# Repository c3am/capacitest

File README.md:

# capacitest
A low cost dual cell battery capacity tester with an oled screen using the ch32v003 microcontroller.

# discharge-tester (old version, unfinished)
In the discharge-tester directory is a pcb with mosfets used as variable resistors for discharging the cells.
It uses LMV358's as current sense amplifiers across 1 Ohm current sense resistors.
I did not get this setup to work, because the built-in adc gave me very jittery values.
Maybe there is something wrong with my circuit, or you just have to software filter the adc values.

# bidirectional-tester (current version, under development)
This is the newer version, which uses bidirectional buck-boost converters for charging the cells from an external ~12V battery/discharging them into that battery.

- ADS 1115 for current and voltage sensing
- ina181a2 + ref2020(2V Vref) for current sense amplification
- ir2101 low+high side mosfet drivers
- ceramic capacitors only
- the two bidirectional buck-/boost-converters each have 1uH SMD inductors, 200uF on the cell and 66uF capacitance on the ~12V battery side
- 0.9" i2c oled screen

## development status/roadmap:
| step                          | status        |
| ----------------------------- | ------------- |
| schematic design              | [done]        |
| PCB design                    | [done]        |
| get PCB and other components  | [done]        |
| assemble board                | [...]         |
| test board/write code         | [not started] |
| if not working, repeat        |               |
| finalize code and put online  | [not started] |

(last updated: 2025-05-08)

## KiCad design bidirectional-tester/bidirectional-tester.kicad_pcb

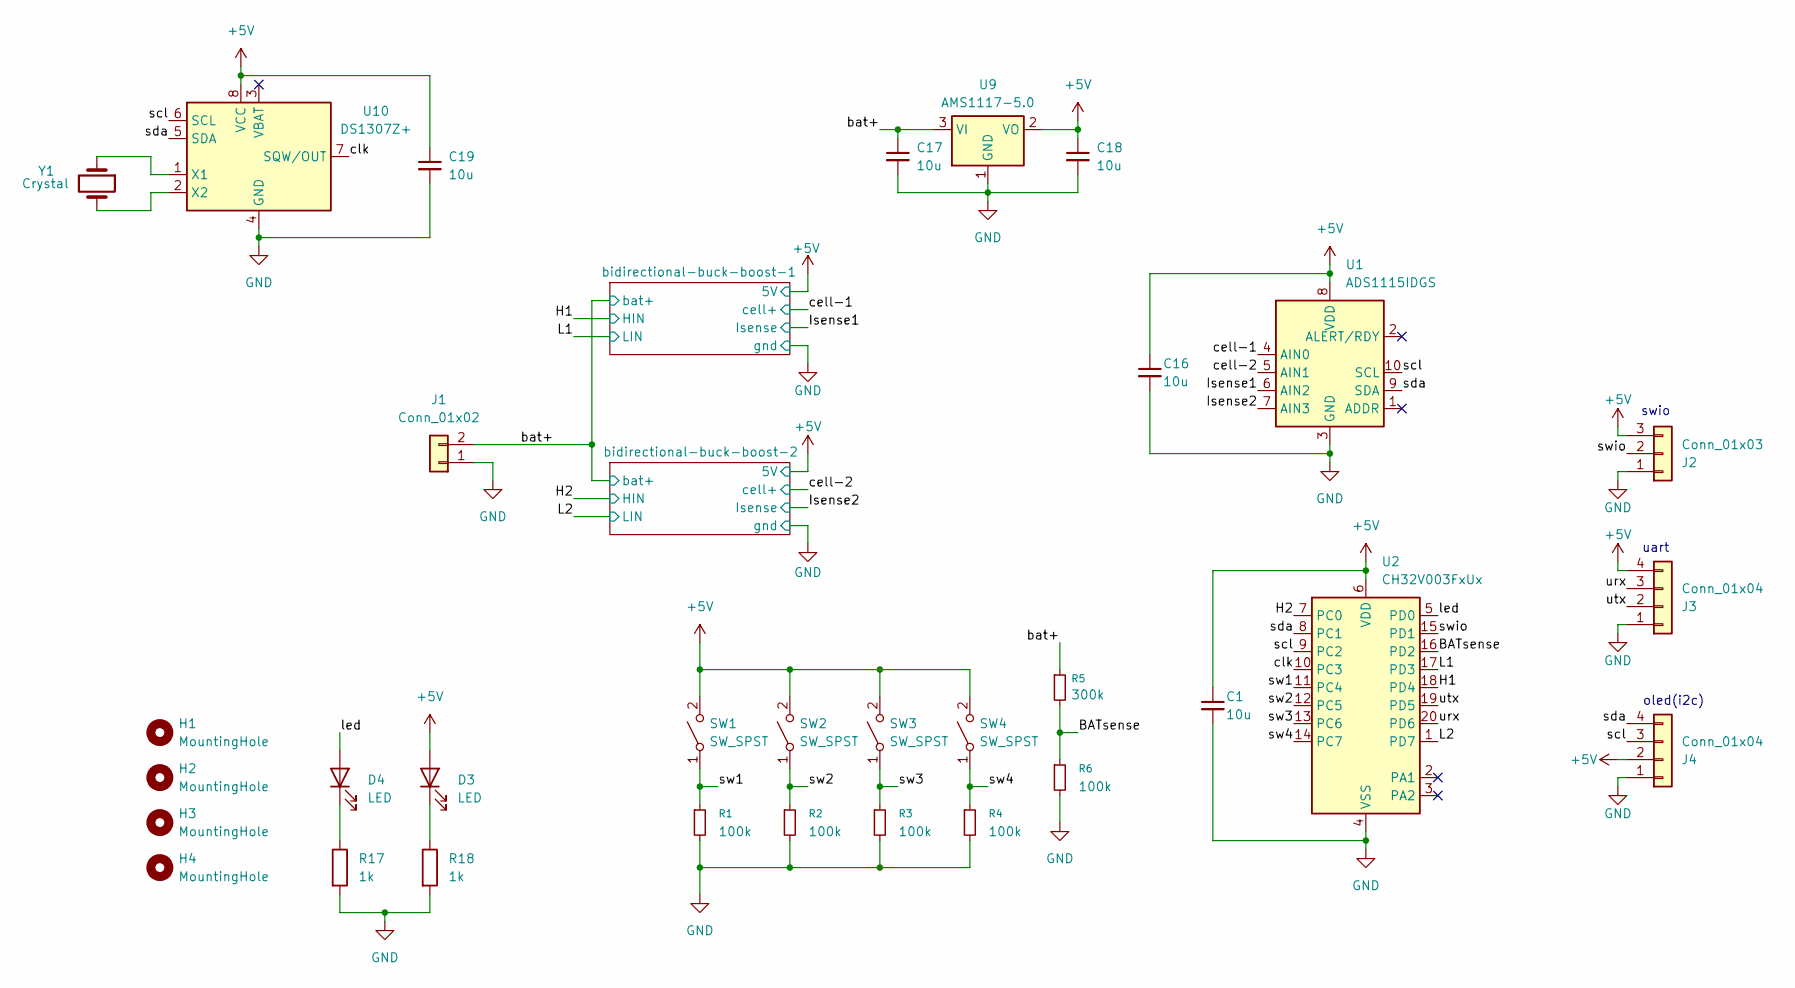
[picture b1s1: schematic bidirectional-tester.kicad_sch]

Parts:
C1, C16, C18, C19: 10u; C_0603_1608Metric
C17: 10u; C_0805_2012Metric
D3, D4: LED; LED_0603_1608Metric
H1, H2, H3, H4: MountingHole; MountingHole_3.2mm_M3
J1: Conn_01x02; screw-terminal_5mm_x2
J2: Conn_01x03; PinHeader_1x03_P2.54mm_Vertical
J3: Conn_01x04; PinHeader_1x04_P2.54mm_Vertical
J4: Conn_01x04; module-oled-0.9inch
R1, R2, R3, R4, R6: 100k; R_0603_1608Metric
R5: 300k; R_0603_1608Metric
R17, R18: 1k; R_0603_1608Metric
SW1, SW2, SW3, SW4: SW_SPST; switch
U1: ADS1115IDGS; TSSOP-10_3x3mm_P0.5mm
U2: CH32V003FxUx; QFN-20-1EP_3x3mm_P0.4mm_EP1.65x1.65mm
U9: AMS1117-5.0; SOT-223-3_TabPin2
U10: DS1307Z+; SOIC-8_3.9x4.9mm_P1.27mm
Y1: Crystal; Crystal_SMD_3215-2Pin_3.2x1.5mm

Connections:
+5V: C1.1, C16.1, C18.1, C19.1, D3.2 (A), J2.3, J3.4, J4.2, SW1.2 (B), SW2.2 (B), SW3.2 (B), SW4.2 (B), U1.8 (VDD), U2.6 (VDD), U9.2 (VO), U10.8 (VCC); also elsewhere on the board
/BATsense: R5.2, R6.1, U2.16 (PD2)
/H1: U2.18 (PD4); also elsewhere on the board
/H2: U2.7 (PC0); also elsewhere on the board
/Isense1: U1.6 (AIN2); also elsewhere on the board
/Isense2: U1.7 (AIN3); also elsewhere on the board
/L1: U2.17 (PD3); also elsewhere on the board
/L2: U2.1 (PD7); also elsewhere on the board
/bat+: C17.1, J1.2, R5.1, U9.3 (VI); also elsewhere on the board
/cell-1: U1.4 (AIN0); also elsewhere on the board
/cell-2: U1.5 (AIN1); also elsewhere on the board
/clk: U2.10 (PC3), U10.7 (SQW/OUT)
/led: D4.2 (A), U2.5 (PD0)
/scl: J4.3, U1.10 (SCL), U2.9 (PC2), U10.6 (SCL)
/sda: J4.4, U1.9 (SDA), U2.8 (PC1), U10.5 (SDA)
/sw1: R1.1, SW1.1 (A), U2.11 (PC4)
/sw2: R2.1, SW2.1 (A), U2.12 (PC5)
/sw3: R3.1, SW3.1 (A), U2.13 (PC6)
/sw4: R4.1, SW4.1 (A), U2.14 (PC7)
/swio: J2.2, U2.15 (PD1)
/urx: J3.3, U2.20 (PD6)
/utx: J3.2, U2.19 (PD5)
GND: C1.2, C16.2, C17.2, C18.2, C19.2, J1.1, J2.1, J3.1, J4.1, R1.2, R2.2, R3.2, R4.2, R6.2, R17.2, R18.2, U1.3 (GND), U2.4 (VSS), U2.21 (VSS), U9.1 (GND), U10.4 (GND); also elsewhere on the board
unnamed: D3.1 (K), R18.1
unnamed: D4.1 (K), R17.1
unnamed: U10.1 (X1), Y1.1
unnamed: U10.2 (X2), Y1.2

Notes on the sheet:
swio
oled(i2c)
uart

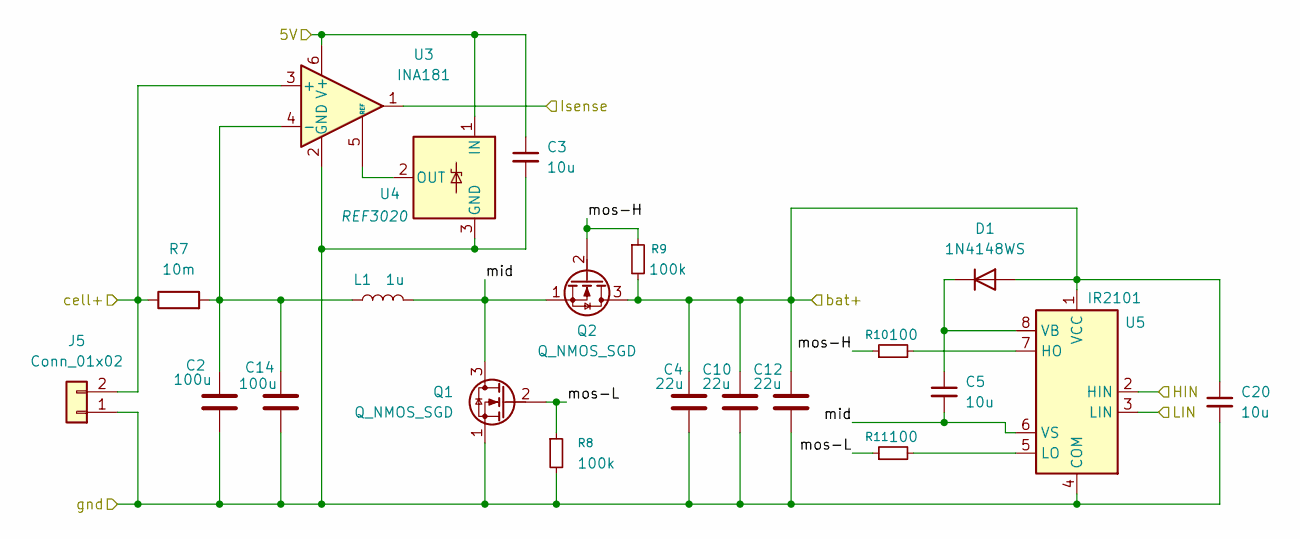
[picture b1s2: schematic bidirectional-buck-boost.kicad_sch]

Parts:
C2, C14: 100u; C_1206_3216Metric
C3, C5, C20: 10u; C_0603_1608Metric
C4, C10, C12: 22u; C_0805_2012Metric
D1: 1N4148WS; D_SOD-323
J5: Conn_01x02; screw-terminal_5mm_x2
L1: 1u; L_Changjiang_FXL0630
Q1, Q2: Q_NMOS_SGD; PQFN-8-EP_6x5mm_P1.27mm_Generic
R7: 10m; R_2512_6332Metric
R8, R9: 100k; R_0603_1608Metric
R10, R11: 100; R_0603_1608Metric
U3: INA181; SOT-23-6
U4: REF3020; SOT-23
U5: IR2101; SOIC-8_3.9x4.9mm_P1.27mm

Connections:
+5V: C3.1, U3.6 (V+), U4.1 (IN); also elsewhere on the board
/H1: U5.2 (HIN); also elsewhere on the board
/Isense1: U3.1; also elsewhere on the board
/L1: U5.3 (LIN); also elsewhere on the board
/bat+: C4.1, C10.1, C12.1, C20.1, D1.2 (A), Q2.3 (D), R9.2, U5.1 (VCC); also elsewhere on the board
/bidirectional-buck-boost-1/mid: C5.2, L1.2, Q1.3 (D), Q2.1 (S), U5.6 (VS)
/bidirectional-buck-boost-1/mos-H: Q2.2 (G), R9.1, R10.1
/bidirectional-buck-boost-1/mos-L: Q1.2 (G), R8.1, R11.1
/cell-1: J5.2, R7.1, U3.3 (+); also elsewhere on the board
GND: C2.2, C3.2, C4.2, C10.2, C12.2, C14.2, C20.2, J5.1, Q1.1 (S), R8.2, U3.2 (GND), U4.3 (GND), U5.4 (COM); also elsewhere on the board
unnamed: C5.1, D1.1 (K), U5.8 (VB)
unnamed: C2.1, C14.1, L1.1, R7.2, U3.4 (-)
unnamed: U3.5 (REF), U4.2 (OUT)
unnamed: R10.2, U5.7 (HO)
unnamed: R11.2, U5.5 (LO)

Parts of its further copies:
C6, C15: 100u; C_1206_3216Metric
C7, C9, C21: 10u; C_0603_1608Metric
C8, C11, C13: 22u; C_0805_2012Metric
D2: 1N4148WS; D_SOD-323
J6: Conn_01x02; screw-terminal_5mm_x2
L2: 1u; L_Changjiang_FXL0630
Q3, Q4: Q_NMOS_SGD; PQFN-8-EP_6x5mm_P1.27mm_Generic
R12: 10m; R_2512_6332Metric
R13, R14: 100k; R_0603_1608Metric
R15, R16: 100; R_0603_1608Metric
U6: INA181; SOT-23-6
U7: REF3020; SOT-23
U8: IR2101; SOIC-8_3.9x4.9mm_P1.27mm

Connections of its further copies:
+5V: C7.1, U6.6 (V+), U7.1 (IN); also elsewhere on the board
/H2: U8.2 (HIN); also elsewhere on the board
/Isense2: U6.1; also elsewhere on the board
/L2: U8.3 (LIN); also elsewhere on the board
/bat+: C8.1, C11.1, C13.1, C21.1, D2.2 (A), Q4.3 (D), R14.2, U8.1 (VCC); also elsewhere on the board
/bidirectional-buck-boost-2/mid: C9.2, L2.2, Q3.3 (D), Q4.1 (S), U8.6 (VS)
/bidirectional-buck-boost-2/mos-H: Q4.2 (G), R14.1, R15.1
/bidirectional-buck-boost-2/mos-L: Q3.2 (G), R13.1, R16.1
/cell-2: J6.2, R12.1, U6.3 (+); also elsewhere on the board
GND: C6.2, C7.2, C8.2, C11.2, C13.2, C15.2, C21.2, J6.1, Q3.1 (S), R13.2, U6.2 (GND), U7.3 (GND), U8.4 (COM); also elsewhere on the board
unnamed: C9.1, D2.1 (K), U8.8 (VB)
unnamed: C6.1, C15.1, L2.1, R12.2, U6.4 (-)
unnamed: U6.5 (REF), U7.2 (OUT)
unnamed: R15.2, U8.7 (HO)
unnamed: R16.2, U8.5 (LO)

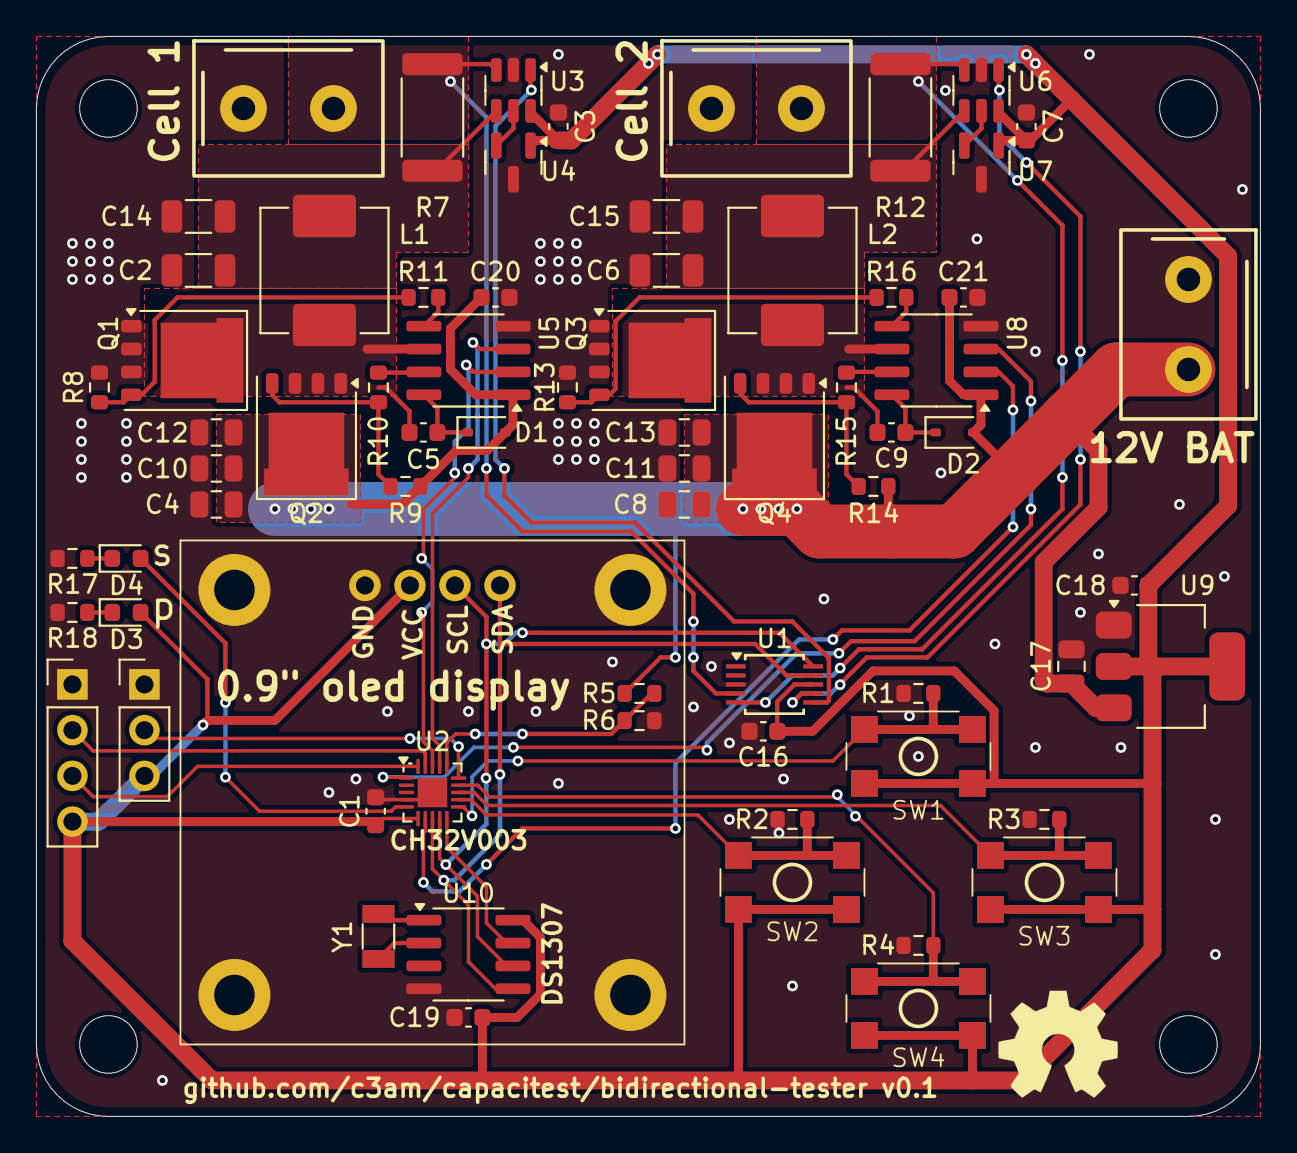
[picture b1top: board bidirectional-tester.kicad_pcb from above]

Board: 2 copper layers, 68.0 x 60.0 mm, 74 parts (0 on the bottom side), 43 nets.

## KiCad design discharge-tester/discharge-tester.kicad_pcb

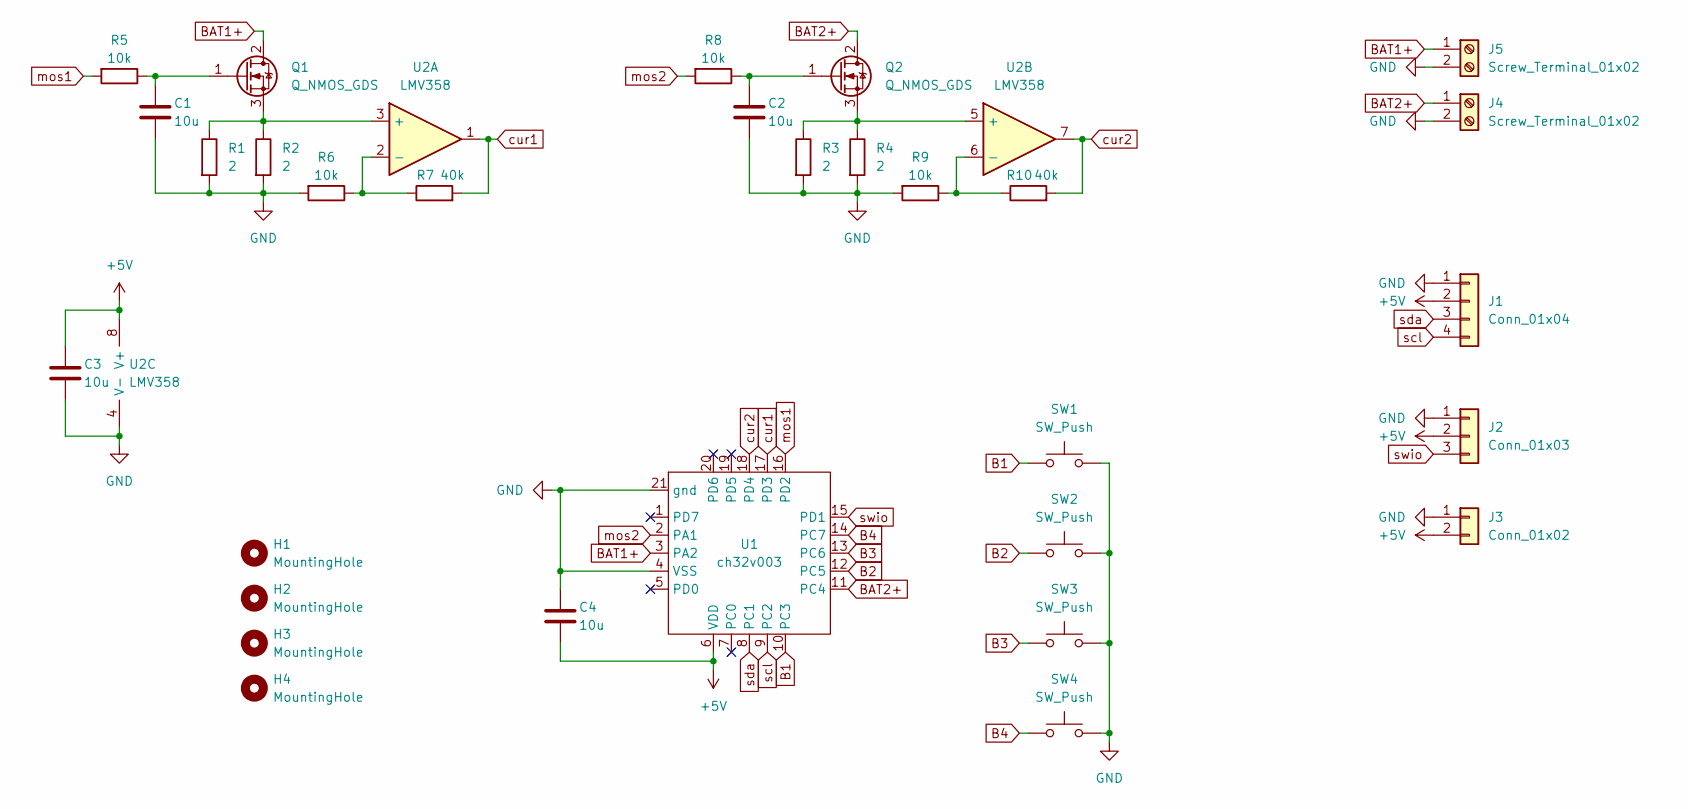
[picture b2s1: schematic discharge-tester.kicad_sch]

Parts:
C1, C2, C3, C4: 10u; C_0603_1608Metric
H1, H2, H3, H4: MountingHole; MountingHole_3.2mm_M3
J1: Conn_01x04; module-oled-0.96
J2: Conn_01x03; pin-header-2.5mm-3
J3: Conn_01x02; pin-header-2.5mm-2
J4, J5: Screw_Terminal_01x02; screw-terminal-P5.00mm-1x02
Q1, Q2: Q_NMOS_GDS; TO-252-2
R1, R2, R3, R4: 2; R_2512_6332Metric
R5, R6, R8, R9: 10k; R_0603_1608Metric
R7, R10: 40k; R_0603_1608Metric
SW1, SW2, SW3, SW4: SW_Push; sw-4.5mm
U1: ch32v003; QFN-20-1EP_3x3mm_P0.4mm_EP1.65x1.65mm
U2: LMV358; SOP-8_3.9x4.9mm_P1.27mm

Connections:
+5V: C3.1, C4.2, J1.2, J2.2, J3.2, U1.6 (VDD), U2.8 (V+)
B1: SW1.1, U1.10 (PC3)
B2: SW2.1, U1.12 (PC5)
B3: SW3.1, U1.13 (PC6)
B4: SW4.1, U1.14 (PC7)
BAT1+: J5.1, Q1.2 (D), U1.3 (PA2)
BAT2+: J4.1, Q2.2 (D), U1.11 (PC4)
GND: C1.2, C2.2, C3.2, C4.1, J1.1, J2.1, J3.1, J4.2, J5.2, R1.2, R2.2, R3.2, R4.2, R6.2, R9.2, SW1.2, SW2.2, SW3.2, SW4.2, U1.4 (VSS), U1.21 (gnd), U2.4 (V-)
unnamed: C1.1, Q1.1 (G), R5.1
unnamed: Q1.3 (S), R1.1, R2.1, U2.3 (+)
unnamed: C2.1, Q2.1 (G), R8.1
unnamed: Q2.3 (S), R3.1, R4.1, U2.5 (+)
unnamed: R6.1, R7.1, U2.2 (-)
unnamed: R9.1, R10.1, U2.6 (-)
cur1: R7.2, U1.17 (PD3), U2.1
cur2: R10.2, U1.18 (PD4), U2.7
mos1: R5.2, U1.16 (PD2)
mos2: R8.2, U1.2 (PA1)
scl: J1.4, U1.9 (PC2)
sda: J1.3, U1.8 (PC1)
swio: J2.3, U1.15 (PD1)

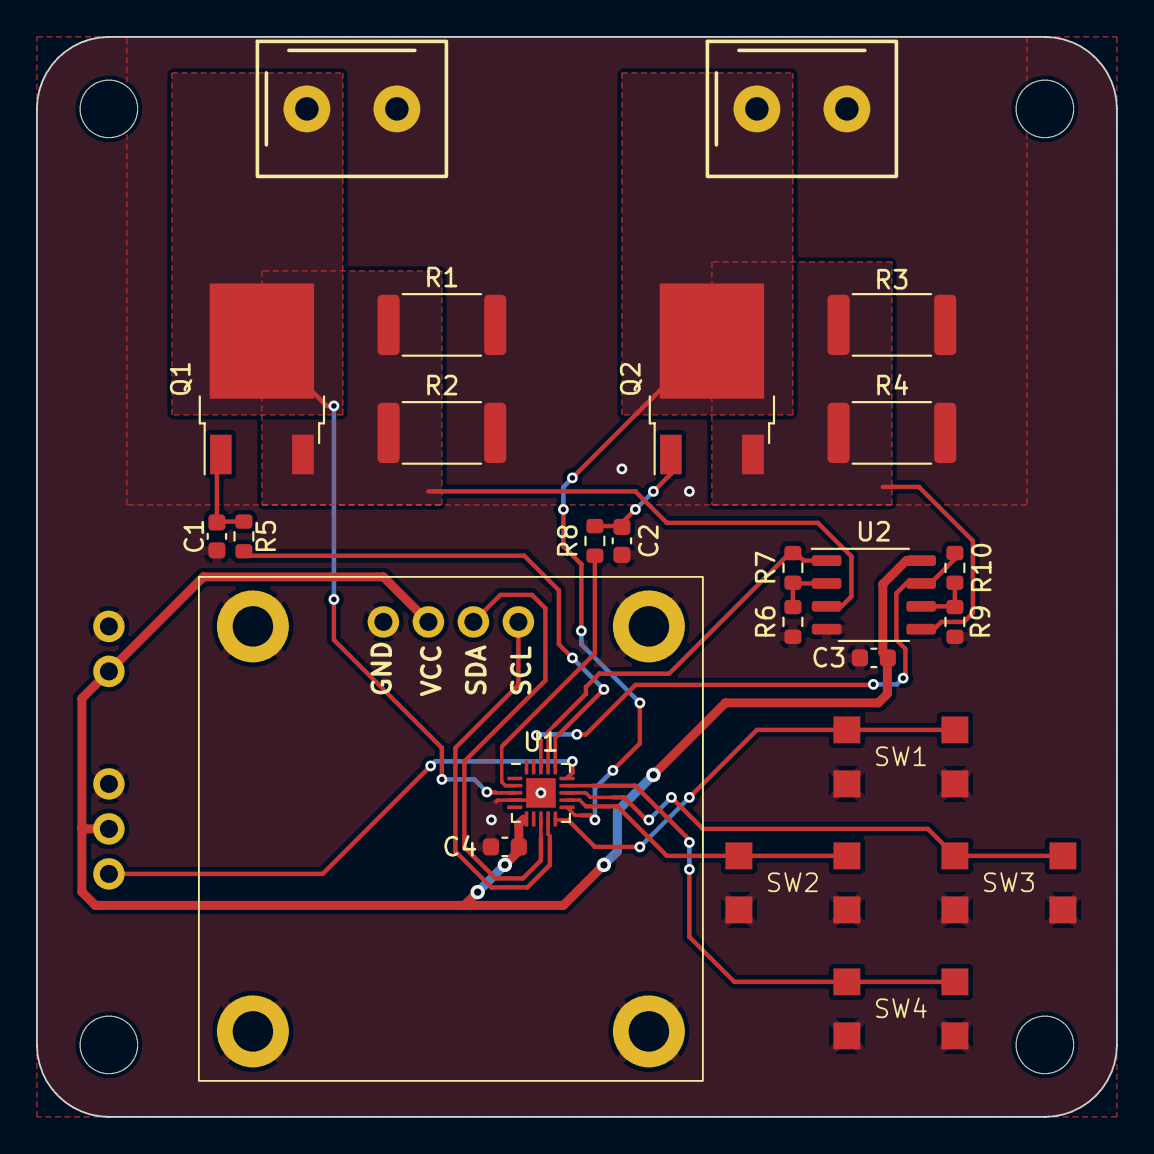
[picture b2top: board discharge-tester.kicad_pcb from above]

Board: 2 copper layers, 60.0 x 60.0 mm, 31 parts (0 on the bottom side), 21 nets.

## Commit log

2023-12-02 upload initial project files
2025-05-08 version 0.1
2025-05-08 removed unnecessary cad files
2025-05-08 improved README
2025-05-08 added silkscreen screw terminal descriptions
2025-05-08 removed output files, will be releases in the future
2025-05-08 removed backup folders
2025-05-08 added indicator leds
2025-05-08 added indicator leds 2 cause it didnt work
2025-05-08 added indicator leds 3 lol
2025-06-02 updated progress bar
